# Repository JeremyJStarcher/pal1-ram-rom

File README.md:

#Breaking change #2

# pal1-ram-rom

Configurable RAM ROM for the PAL-1 (kim-1 clone)

This project is still under development to replace the RAM/ROM and IO expansion board with a Pi Pico.

Current state:  The prototype worked after some manual board rework.

Trying to take over the DEN line via software so all ICs except the Pi Pico can be removed from the board.

## KIM-1 Memory Map

* K0 $0000 - $03FF 1024 bytes of RAM (8*6102)
* K1 $0400 - $07FF free
* K2 $0800 - $0BFF free
* K3 $0C00 - $0FFF free
* K4 $1000 - $13FF free
* K5 $1400 - $16FF free
  * $1700 - $173F I/O, timer of 6530-003
  * $1740 - $177F I/O, timer of 6530-002
  * $1780 - $17BF 64 bytes RAM of 6530-003
  * $17C0 - $17FF 64 bytes RAM of 6530-002
* K6 $1800 - $1BFF 1024 bytes ROM of 6530-003
* K7 $1C00 - $1FFF 1024 bytes ROM of 6530-002

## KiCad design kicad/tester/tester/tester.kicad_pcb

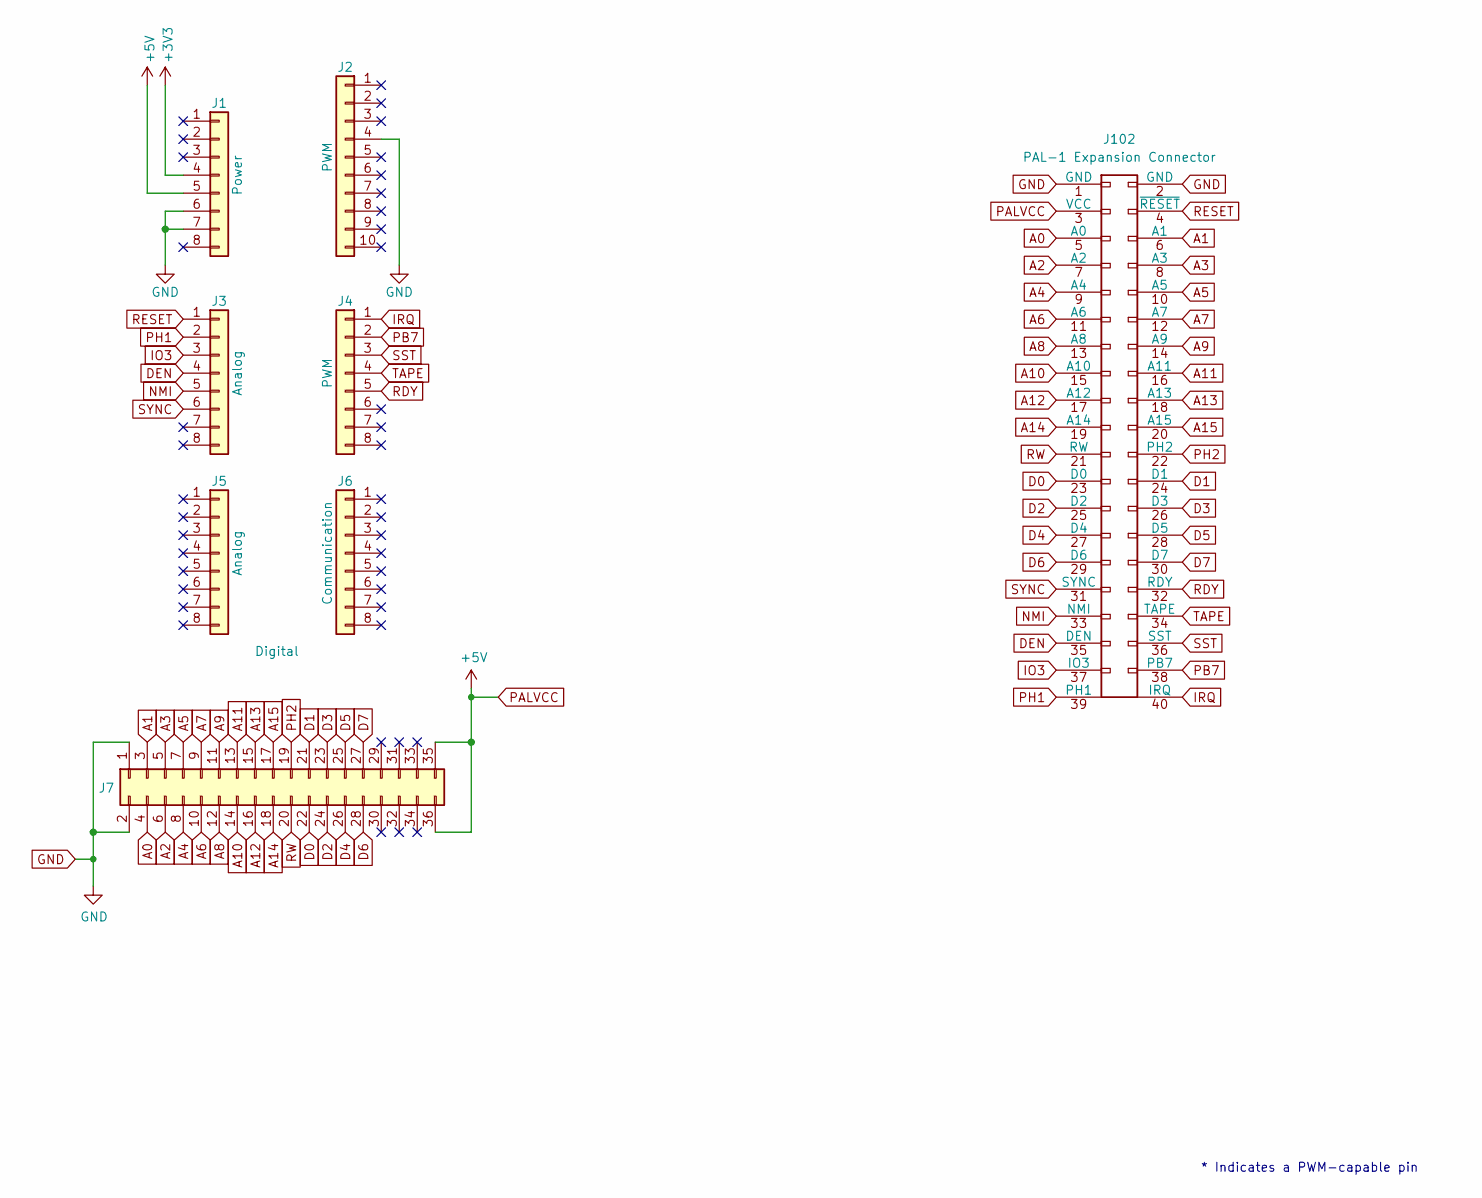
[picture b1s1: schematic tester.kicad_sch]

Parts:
J1: Power; PinSocket_1x08_P2.54mm_Vertical
J2: PWM; PinSocket_1x10_P2.54mm_Vertical
J3, J5: Analog; PinSocket_1x08_P2.54mm_Vertical
J4: PWM; PinSocket_1x08_P2.54mm_Vertical
J6: Communication; PinSocket_1x08_P2.54mm_Vertical
J7: Digital; PinSocket_2x18_P2.54mm_Vertical
J102: PAL-1 Expansion Connector; PinHeader_2x20_P2.54mm_Vertical

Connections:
+3V3: J1.4
A0: J7.4, J102.5 (A0)
A1: J7.3, J102.6 (A1)
A2: J7.6, J102.7 (A2)
A3: J7.5, J102.8 (A3)
A4: J7.8, J102.9 (A4)
A5: J7.7, J102.10 (A5)
A6: J7.10, J102.11 (A6)
A7: J7.9, J102.12 (A7)
A8: J7.12, J102.13 (A8)
A9: J7.11, J102.14 (A9)
A10: J7.14, J102.15 (A10)
A11: J7.13, J102.16 (A11)
A12: J7.16, J102.17 (A12)
A13: J7.15, J102.18 (A13)
A14: J7.18, J102.19 (A14)
A15: J7.17, J102.20 (A15)
D0: J7.22, J102.23 (D0)
D1: J7.21, J102.24 (D1)
D2: J7.24, J102.25 (D2)
D3: J7.23, J102.26 (D3)
D4: J7.26, J102.27 (D4)
D5: J7.25, J102.28 (D5)
D6: J7.28, J102.29 (D6)
D7: J7.27, J102.30 (D7)
DEN: J3.4, J102.35 (DEN)
GND: J1.6, J1.7, J2.4, J7.1, J7.2, J102.1 (GND), J102.2 (GND)
IO3: J3.3, J102.37 (IO3)
IRQ: J4.1, J102.40 (IRQ)
NMI: J3.5, J102.33 (NMI)
PALVCC: J1.5, J7.35, J7.36, J102.3 (VCC)
PB7: J4.2, J102.38 (PB7)
PH1: J3.2, J102.39 (PH1)
PH2: J7.19, J102.22 (PH2)
RDY: J4.5, J102.32 (RDY)
RESET: J3.1, J102.4 (~RESET)
RW: J7.20, J102.21 (RW)
SST: J4.3, J102.36 (SST)
SYNC: J3.6, J102.31 (SYNC)
TAPE: J4.4, J102.34 (TAPE)

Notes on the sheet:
* Indicates a PWM-capable pin

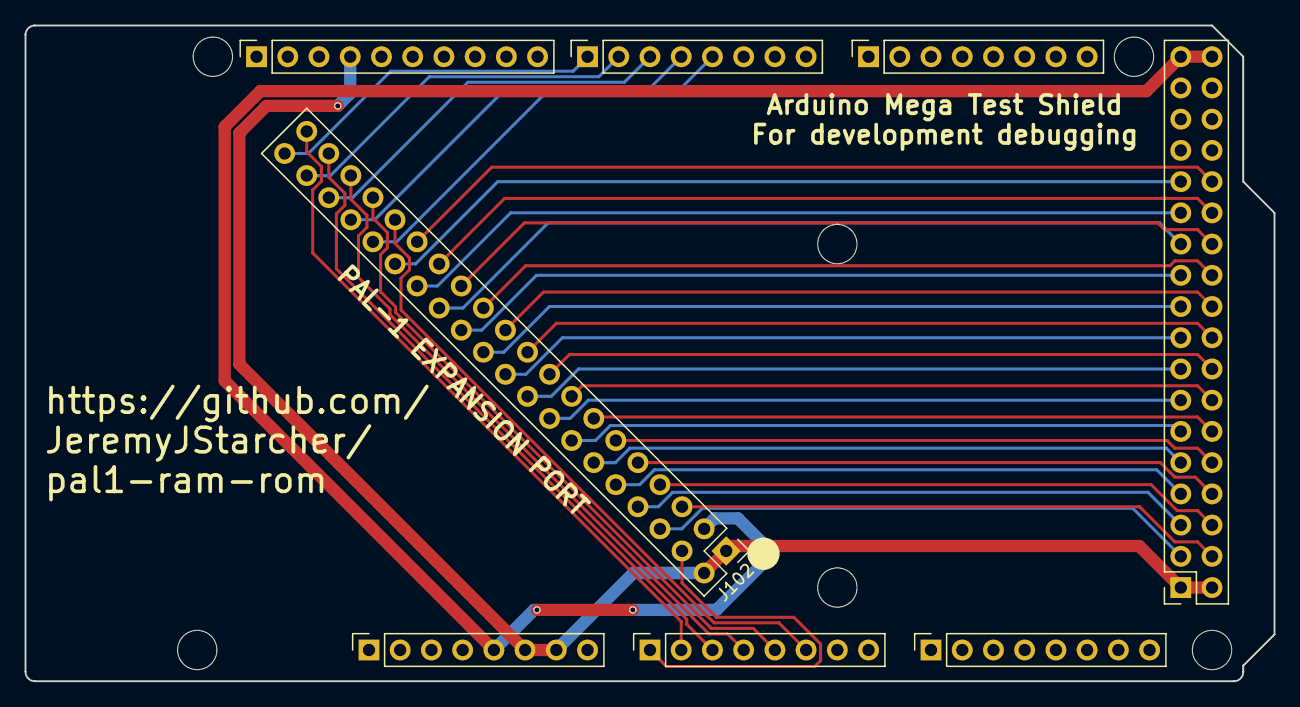
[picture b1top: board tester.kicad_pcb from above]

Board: 2 copper layers, 101.6 x 53.3 mm, 14 parts (0 on the bottom side), 39 nets.

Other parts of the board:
MH1, MH2, MH3, MH4, MH5, MH6: MountingHole_3.2mm

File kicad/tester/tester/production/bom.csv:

Designator,Footprint,Quantity,Value,LCSC Part #
J1,PinSocket_1x08_P2.54mm_Vertical,1,Power,
J102,PinHeader_2x20_P2.54mm_Vertical,1,PAL-1 Expansion Connector,
J2,PinSocket_1x10_P2.54mm_Vertical,1,PWM,
"J3, J5",PinSocket_1x08_P2.54mm_Vertical,2,Analog,
J4,PinSocket_1x08_P2.54mm_Vertical,1,PWM,
J6,PinSocket_1x08_P2.54mm_Vertical,1,Communication,
J7,PinSocket_2x18_P2.54mm_Vertical,1,Digital,

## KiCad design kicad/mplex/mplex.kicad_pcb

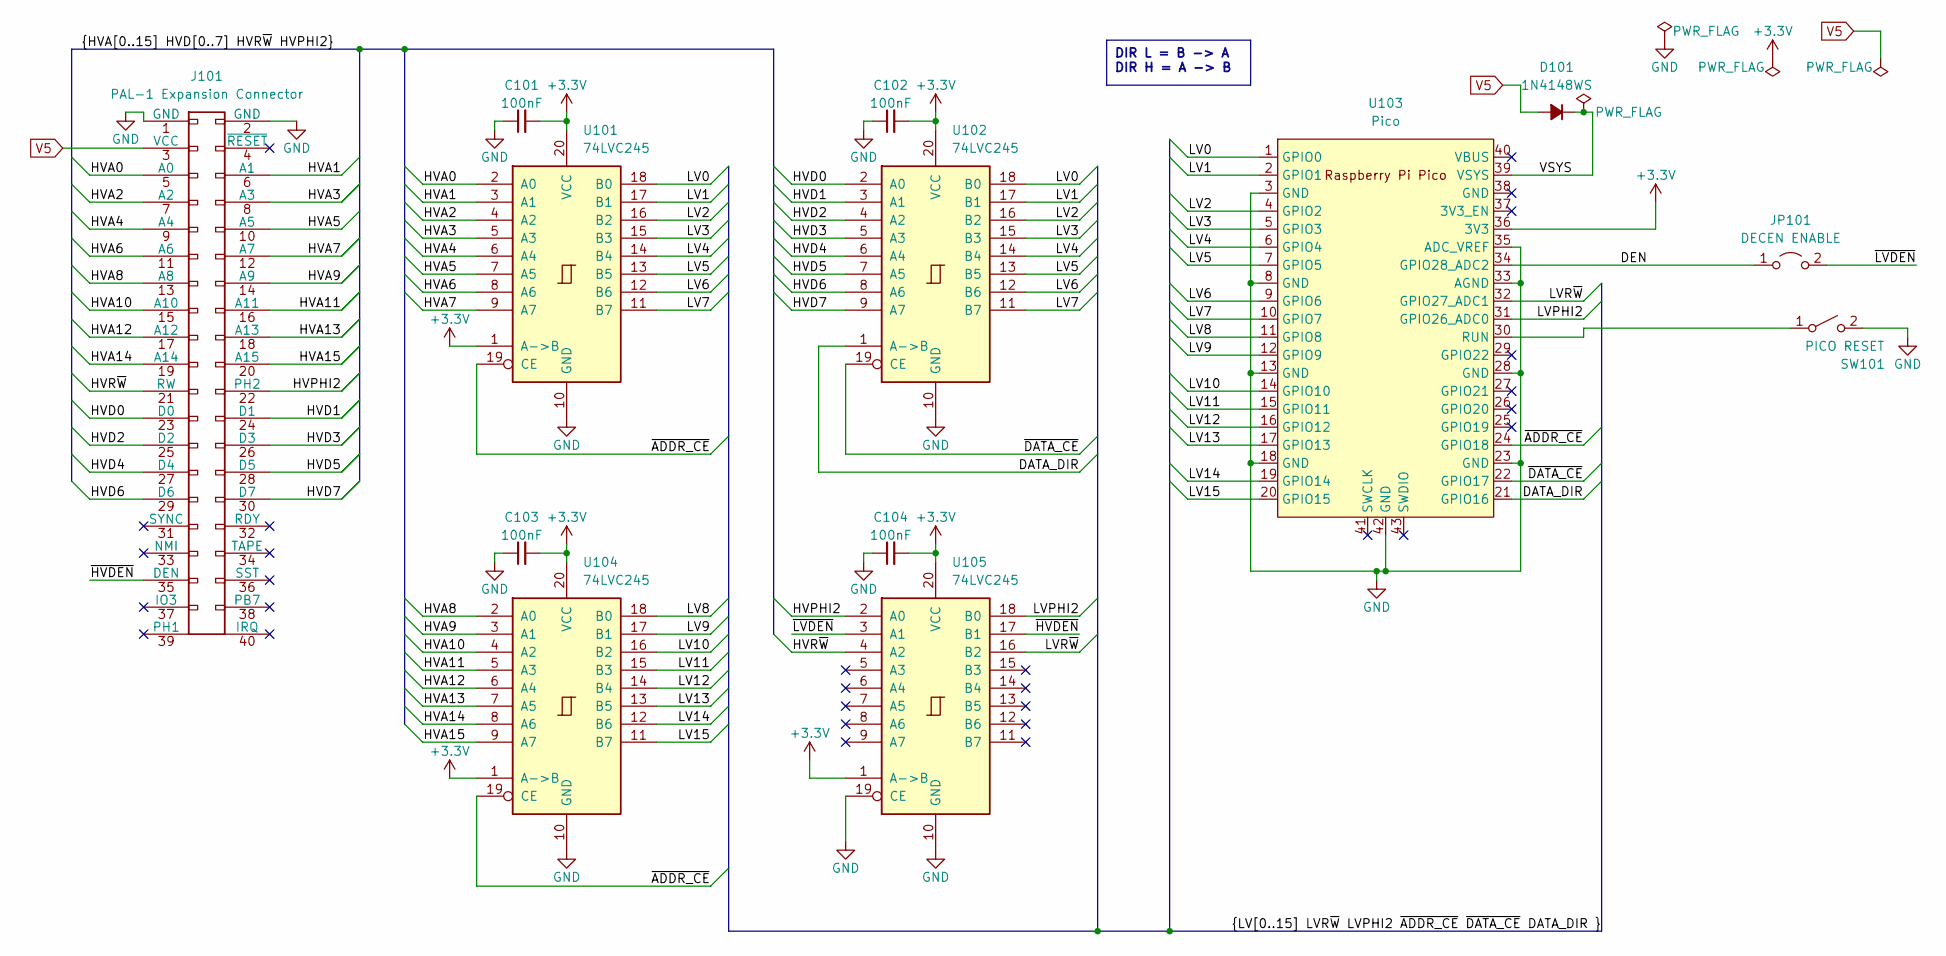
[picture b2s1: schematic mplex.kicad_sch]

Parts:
C101, C102, C103, C104: 100nF; C_Disc_D4.7mm_W2.5mm_P5.00mm
D101: 1N4148WS; D_A-405_P7.62mm_Horizontal; JLCPCB C2128
J101: PAL-1 Expansion Connector; PinHeader_2x20_P2.54mm_Vertical
JP101: DECEN ENABLE; PinHeader_1x02_P2.54mm_Vertical
SW101: PICO RESET; SW_PUSH_6mm_H4.3mm; MFG# TC-6601-6-260G; JLCPCB C2845316
U101, U102, U104, U105: 74LVC245; DIP-20_W7.62mm_Socket_LongPads
U103: Pico; RPi_Pico_SMD_TH

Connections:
+3.3V: C101.2, C102.2, C103.2, C104.2, U101.1 (A->B), U101.20 (VCC), U102.20 (VCC), U103.36 (3V3), U104.1 (A->B), U104.20 (VCC), U105.1 (A->B), U105.20 (VCC)
/DATA_DIR: U102.1 (A->B), U103.21 (GPIO16)
/DEN: JP101.1 (A), U103.34 (GPIO28_ADC2)
/HVA0: J101.5 (A0), U101.2 (A0)
/HVA1: J101.6 (A1), U101.3 (A1)
/HVA2: J101.7 (A2), U101.4 (A2)
/HVA3: J101.8 (A3), U101.5 (A3)
/HVA4: J101.9 (A4), U101.6 (A4)
/HVA5: J101.10 (A5), U101.7 (A5)
/HVA6: J101.11 (A6), U101.8 (A6)
/HVA7: J101.12 (A7), U101.9 (A7)
/HVA8: J101.13 (A8), U104.2 (A0)
/HVA9: J101.14 (A9), U104.3 (A1)
/HVA10: J101.15 (A10), U104.4 (A2)
/HVA11: J101.16 (A11), U104.5 (A3)
/HVA12: J101.17 (A12), U104.6 (A4)
/HVA13: J101.18 (A13), U104.7 (A5)
/HVA14: J101.19 (A14), U104.8 (A6)
/HVA15: J101.20 (A15), U104.9 (A7)
/HVD0: J101.23 (D0), U102.2 (A0)
/HVD1: J101.24 (D1), U102.3 (A1)
/HVD2: J101.25 (D2), U102.4 (A2)
/HVD3: J101.26 (D3), U102.5 (A3)
/HVD4: J101.27 (D4), U102.6 (A4)
/HVD5: J101.28 (D5), U102.7 (A5)
/HVD6: J101.29 (D6), U102.8 (A6)
/HVD7: J101.30 (D7), U102.9 (A7)
/HVPHI2: J101.22 (PH2), U105.2 (A0)
/HVR~W: J101.21 (RW), U105.4 (A2)
/LV0: U101.18 (B0), U102.18 (B0), U103.1 (GPIO0)
/LV1: U101.17 (B1), U102.17 (B1), U103.2 (GPIO1)
/LV2: U101.16 (B2), U102.16 (B2), U103.4 (GPIO2)
/LV3: U101.15 (B3), U102.15 (B3), U103.5 (GPIO3)
/LV4: U101.14 (B4), U102.14 (B4), U103.6 (GPIO4)
/LV5: U101.13 (B5), U102.13 (B5), U103.7 (GPIO5)
/LV6: U101.12 (B6), U102.12 (B6), U103.9 (GPIO6)
/LV7: U101.11 (B7), U102.11 (B7), U103.10 (GPIO7)
/LV8: U103.11 (GPIO8), U104.18 (B0)
/LV9: U103.12 (GPIO9), U104.17 (B1)
/LV10: U103.14 (GPIO10), U104.16 (B2)
/LV11: U103.15 (GPIO11), U104.15 (B3)
/LV12: U103.16 (GPIO12), U104.14 (B4)
/LV13: U103.17 (GPIO13), U104.13 (B5)
/LV14: U103.19 (GPIO14), U104.12 (B6)
/LV15: U103.20 (GPIO15), U104.11 (B7)
/LVPHI2: U103.31 (GPIO26_ADC0), U105.18 (B0)
/LVR~W: U103.32 (GPIO27_ADC1), U105.16 (B2)
/VSYS: D101.1 (K), U103.39 (VSYS)
/~ADDR_CE: U101.19 (CE), U103.24 (GPIO18), U104.19 (CE)
/~DATA_CE: U102.19 (CE), U103.22 (GPIO17)
/~HVDEN: J101.35 (DEN), U105.17 (B1)
/~LVDEN: JP101.2 (B), U105.3 (A1)
unnamed: SW101.1 (A), U103.30 (RUN)
V5: D101.2 (A), J101.3 (VCC)

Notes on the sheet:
DIR L = B -> A DIR H = A -> B

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
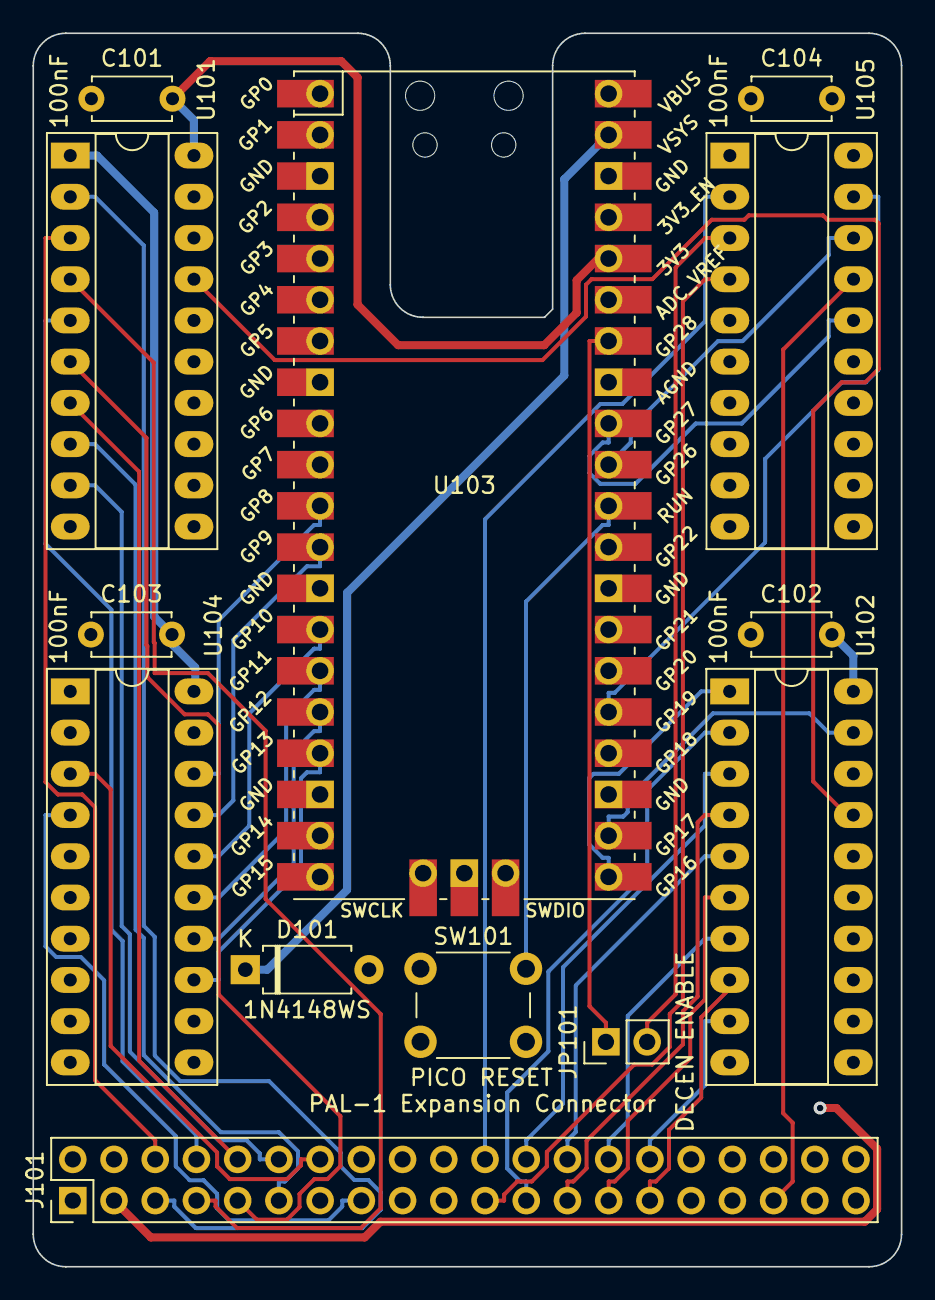
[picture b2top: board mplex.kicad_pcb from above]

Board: 4 copper layers, 53.5 x 76.0 mm, 13 parts (0 on the bottom side), 56 nets.

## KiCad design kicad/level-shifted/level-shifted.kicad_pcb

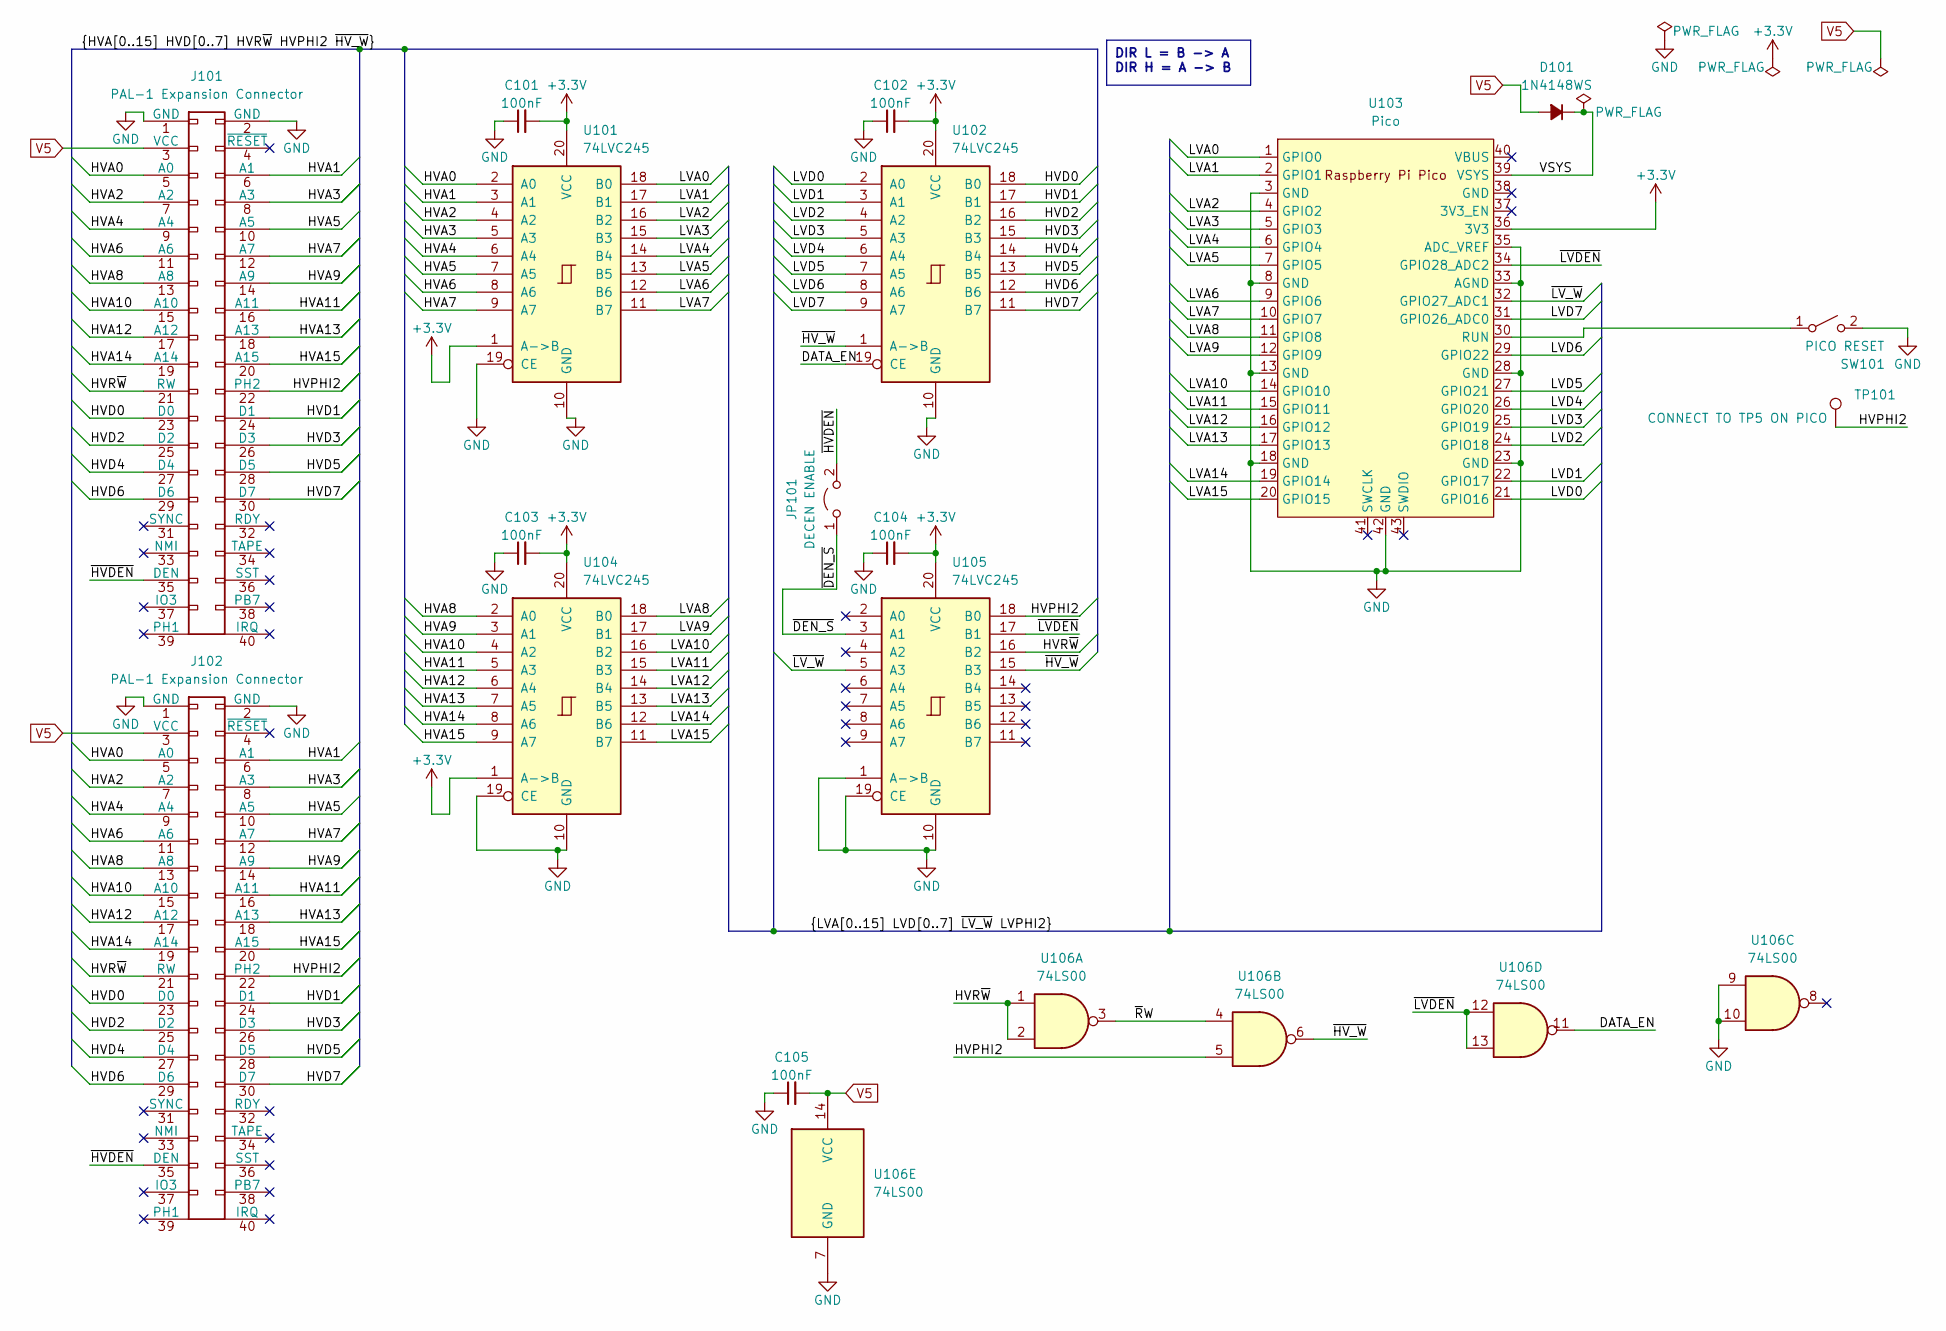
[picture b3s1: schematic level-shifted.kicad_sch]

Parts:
C101, C102, C103, C104: 100nF; C_Disc_D4.7mm_W2.5mm_P5.00mm
C105: 100nF; C_1812_4532Metric_Pad1.57x3.40mm_HandSolder
D101: 1N4148WS; D_A-405_P7.62mm_Horizontal; JLCPCB C2128
J101, J102: PAL-1 Expansion Connector; PinHeader_2x20_P2.54mm_Vertical
JP101: DECEN ENABLE; PinHeader_1x02_P2.54mm_Vertical
SW101: PICO RESET; SW_PUSH_6mm_H4.3mm; MFG# TC-6601-6-260G; JLCPCB C2845316
TP101: CONNECT TO TP5 ON PICO; TestPoint_Pad_2.5x2.5mm
U101, U102, U104, U105: 74LVC245; DIP-20_W7.62mm_Socket_LongPads
U103: Pico; RPi_Pico_SMD_TH
U106: 74LS00; DIP-14_W8.89mm_SMDSocket_LongPads

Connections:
+3.3V: C101.2, C102.2, C103.2, C104.2, U101.1 (A->B), U101.20 (VCC), U102.20 (VCC), U103.36 (3V3), U104.1 (A->B), U104.20 (VCC), U105.20 (VCC)
/DATA_EN: U102.19 (CE), U106.11
/HVA0: J101.5 (A0), J102.5 (A0), U101.2 (A0)
/HVA1: J101.6 (A1), J102.6 (A1), U101.3 (A1)
/HVA2: J101.7 (A2), J102.7 (A2), U101.4 (A2)
/HVA3: J101.8 (A3), J102.8 (A3), U101.5 (A3)
/HVA4: J101.9 (A4), J102.9 (A4), U101.6 (A4)
/HVA5: J101.10 (A5), J102.10 (A5), U101.7 (A5)
/HVA6: J101.11 (A6), J102.11 (A6), U101.8 (A6)
/HVA7: J101.12 (A7), J102.12 (A7), U101.9 (A7)
/HVA8: J101.13 (A8), J102.13 (A8), U104.2 (A0)
/HVA9: J101.14 (A9), J102.14 (A9), U104.3 (A1)
/HVA10: J101.15 (A10), J102.15 (A10), U104.4 (A2)
/HVA11: J101.16 (A11), J102.16 (A11), U104.5 (A3)
/HVA12: J101.17 (A12), J102.17 (A12), U104.6 (A4)
/HVA13: J101.18 (A13), J102.18 (A13), U104.7 (A5)
/HVA14: J101.19 (A14), J102.19 (A14), U104.8 (A6)
/HVA15: J101.20 (A15), J102.20 (A15), U104.9 (A7)
/HVD0: J101.23 (D0), J102.23 (D0), U102.18 (B0)
/HVD1: J101.24 (D1), J102.24 (D1), U102.17 (B1)
/HVD2: J101.25 (D2), J102.25 (D2), U102.16 (B2)
/HVD3: J101.26 (D3), J102.26 (D3), U102.15 (B3)
/HVD4: J101.27 (D4), J102.27 (D4), U102.14 (B4)
/HVD5: J101.28 (D5), J102.28 (D5), U102.13 (B5)
/HVD6: J101.29 (D6), J102.29 (D6), U102.12 (B6)
/HVD7: J101.30 (D7), J102.30 (D7), U102.11 (B7)
/HVPHI2: J101.22 (PH2), J102.22 (PH2), TP101.1, U105.18 (B0), U106.5
/HVR~W: J101.21 (RW), J102.21 (RW), U105.16 (B2), U106.1, U106.2
/LVA0: U101.18 (B0), U103.1 (GPIO0)
/LVA1: U101.17 (B1), U103.2 (GPIO1)
/LVA2: U101.16 (B2), U103.4 (GPIO2)
/LVA3: U101.15 (B3), U103.5 (GPIO3)
/LVA4: U101.14 (B4), U103.6 (GPIO4)
/LVA5: U101.13 (B5), U103.7 (GPIO5)
/LVA6: U101.12 (B6), U103.9 (GPIO6)
/LVA7: U101.11 (B7), U103.10 (GPIO7)
/LVA8: U103.11 (GPIO8), U104.18 (B0)
/LVA9: U103.12 (GPIO9), U104.17 (B1)
/LVA10: U103.14 (GPIO10), U104.16 (B2)
/LVA11: U103.15 (GPIO11), U104.15 (B3)
/LVA12: U103.16 (GPIO12), U104.14 (B4)
/LVA13: U103.17 (GPIO13), U104.13 (B5)
/LVA14: U103.19 (GPIO14), U104.12 (B6)
/LVA15: U103.20 (GPIO15), U104.11 (B7)
/LVD0: U102.2 (A0), U103.21 (GPIO16)
/LVD1: U102.3 (A1), U103.22 (GPIO17)
/LVD2: U102.4 (A2), U103.24 (GPIO18)
/LVD3: U102.5 (A3), U103.25 (GPIO19)
/LVD4: U102.6 (A4), U103.26 (GPIO20)
/LVD5: U102.7 (A5), U103.27 (GPIO21)
/LVD6: U102.8 (A6), U103.29 (GPIO22)
/LVD7: U102.9 (A7), U103.31 (GPIO26_ADC0)
/VSYS: D101.1 (K), U103.39 (VSYS)
/~DEN_S: JP101.1 (A), U105.3 (A1)
/~HVDEN: J101.35 (DEN), J102.35 (DEN), JP101.2 (B)
/~HV_W: U102.1 (A->B), U105.15 (B3), U106.6
/~LVDEN: U103.34 (GPIO28_ADC2), U105.17 (B1), U106.12, U106.13
/~LV_W: U103.32 (GPIO27_ADC1), U105.5 (A3)
/~RW: U106.3, U106.4
GND: C101.1, C102.1, C103.1, C104.1, C105.1, J101.1 (GND), J101.2 (GND), J102.1 (GND), J102.2 (GND), SW101.2 (B), U101.10 (GND), U101.19 (CE), U102.10 (GND), U103.3 (GND), U103.8 (GND), U103.13 (GND), U103.18 (GND), U103.23 (GND), U103.28 (GND), U103.33 (AGND), U103.35 (ADC_VREF), U103.42 (GND), U104.10 (GND), U104.19 (CE), U105.1 (A->B), U105.10 (GND), U105.19 (CE), U106.7 (GND), U106.9, U106.10
unnamed: SW101.1 (A), U103.30 (RUN)
V5: C105.2, D101.2 (A), J101.3 (VCC), J102.3 (VCC), U106.14 (VCC)

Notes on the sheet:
DIR L = B -> A DIR H = A -> B

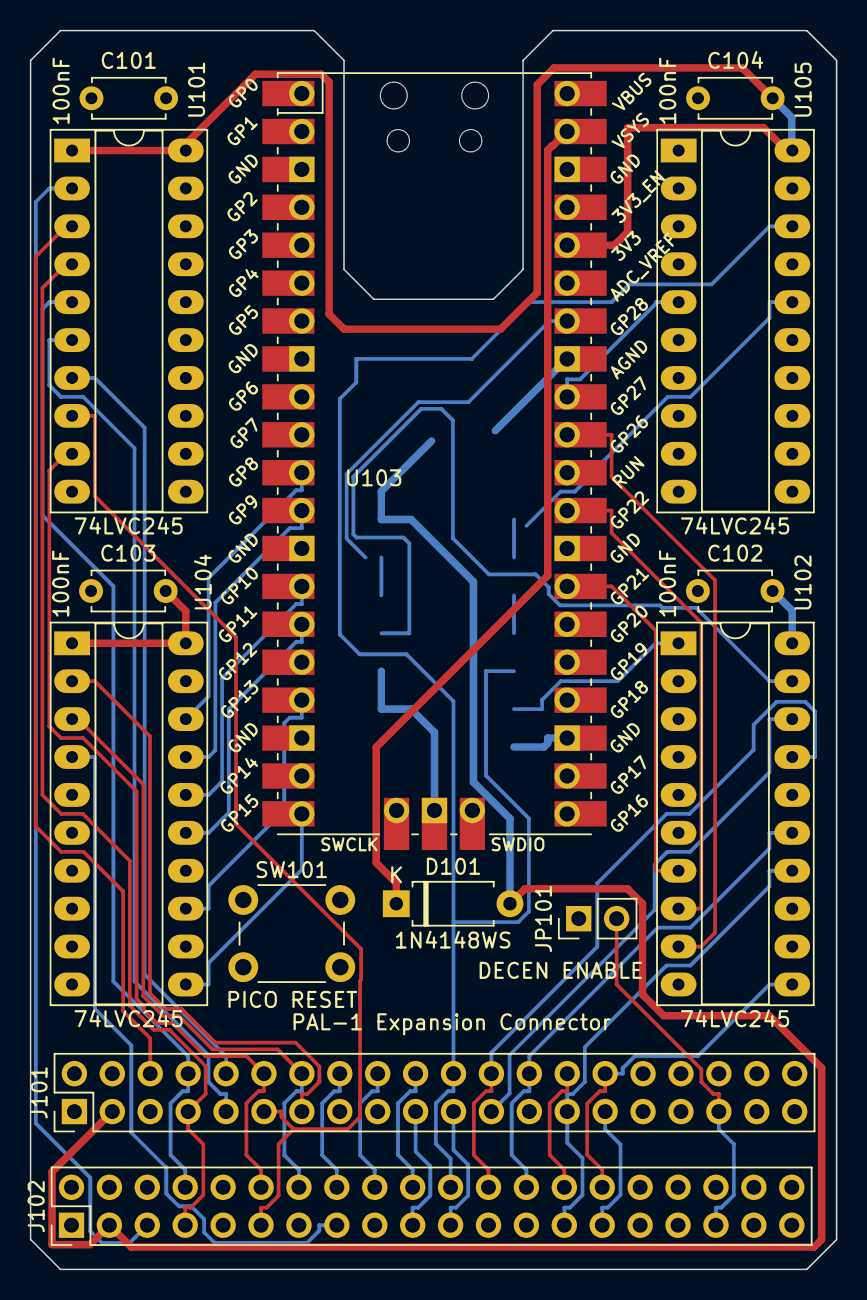
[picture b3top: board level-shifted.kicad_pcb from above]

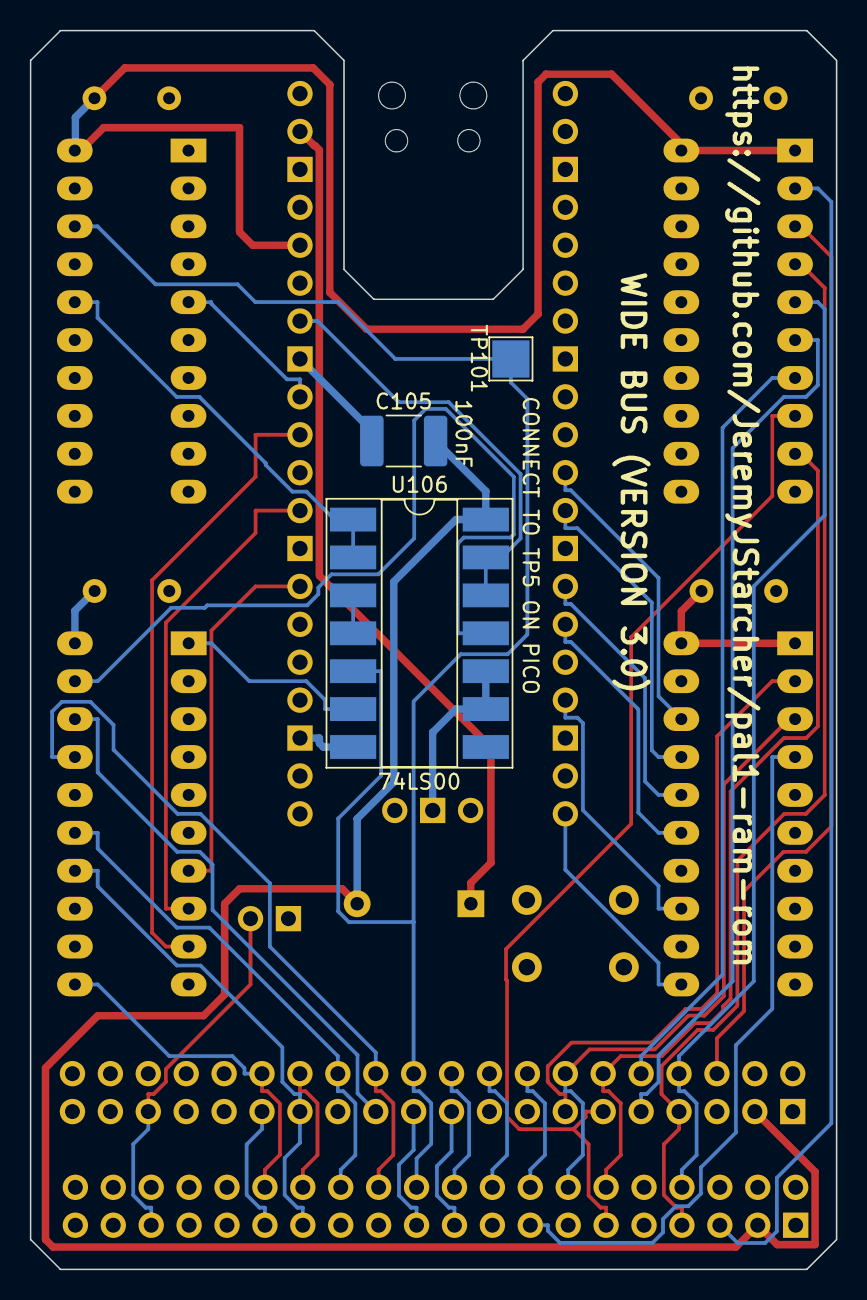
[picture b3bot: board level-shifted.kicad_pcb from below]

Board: 4 copper layers, 54.0 x 83.0 mm, 17 parts (3 on the bottom side), 62 nets.

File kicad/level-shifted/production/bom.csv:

Designator,Footprint,Quantity,Value,LCSC Part #
"C101, C102, C103, C104",C_Disc_D4.7mm_W2.5mm_P5.00mm,4,100nF,
C105,1812,1,100nF,
D101,D_A-405_P7.62mm_Horizontal,1,1N4148WS,
"J101, J102",PinHeader_2x20_P2.54mm_Vertical,2,PAL-1 Expansion Connector,
JP101,PinHeader_1x02_P2.54mm_Vertical,1,DECEN ENABLE,
SW101,SW_PUSH_6mm_H4.3mm,1,PICO RESET,
TP101,TestPoint_Pad_2.5x2.5mm,1,CONNECT TO TP5 ON PICO,
"U101, U102, U104, U105",DIP-20_W7.62mm_Socket_LongPads,4,74LVC245,
U103,RPi_Pico_SMD_TH,1,Pico,
U106,DIP-14_W8.89mm_SMDSocket_LongPads,1,74LS00,

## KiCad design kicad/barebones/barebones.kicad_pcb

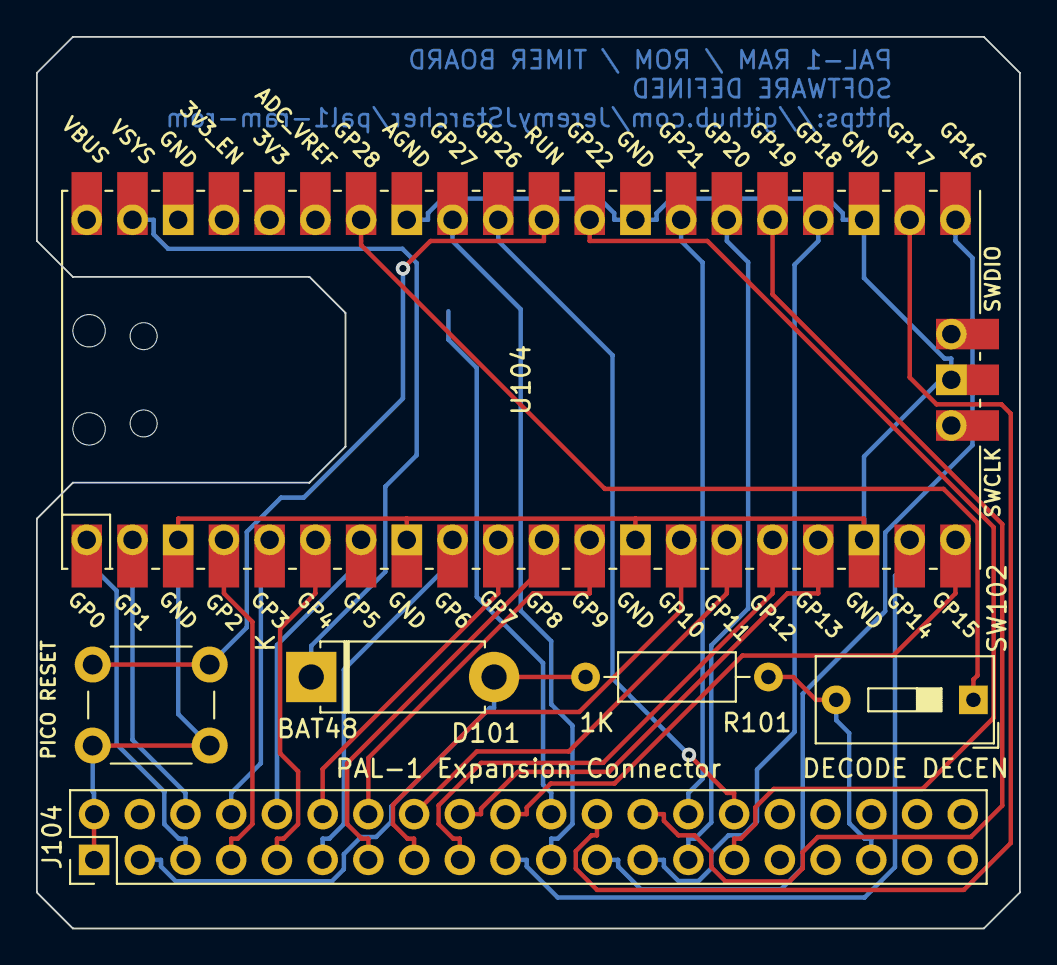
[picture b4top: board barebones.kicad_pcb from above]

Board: 2 copper layers, 54.6 x 49.5 mm, 7 parts (1 on the bottom side), 32 nets.

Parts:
D101: BAT48; D_5W_P10.16mm_Horizontal
J104: PAL-1 Expansion Connector; PinHeader_2x20_P2.54mm_Vertical
R101: 1K; R_Axial_DIN0207_L6.3mm_D2.5mm_P10.16mm_Horizontal
SW101: PICO RESET; SW_PUSH_6mm
SW102: SW_DIP_x01; SW_DIP_SPSTx01_Slide_9.78x4.72mm_W7.62mm_P2.54mm
TP101: CONNECT TO TP5 ON PICO; TestPoint_Pad_2.5x2.5mm
U104: Pico; RPi_Pico_SMD_TH

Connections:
A0: J104.5 (A0), U104.1 (GPIO0)
A1: J104.6 (A1), U104.2 (GPIO1)
A2: J104.7 (A2), U104.4 (GPIO2)
A3: J104.8 (A3), U104.5 (GPIO3)
A4: J104.9 (A4), U104.6 (GPIO4)
A5: J104.10 (A5), U104.7 (GPIO5)
A6: J104.11 (A6), U104.9 (GPIO6)
A7: J104.12 (A7), U104.10 (GPIO7)
A8: J104.13 (A8), U104.11 (GPIO8)
A9: J104.14 (A9), U104.12 (GPIO9)
A10: J104.15 (A10), U104.14 (GPIO10)
A11: J104.16 (A11), U104.15 (GPIO11)
A12: J104.17 (A12), U104.16 (GPIO12)
A13: J104.18 (A13), U104.17 (GPIO13)
A14: J104.19 (A14), U104.19 (GPIO14)
A15: J104.20 (A15), U104.20 (GPIO15)
D0: J104.23 (D0), U104.21 (GPIO16)
D1: J104.24 (D1), U104.22 (GPIO17)
D2: J104.25 (D2), U104.24 (GPIO18)
D3: J104.26 (D3), U104.25 (GPIO19)
D4: J104.27 (D4), U104.26 (GPIO20)
D5: J104.28 (D5), U104.27 (GPIO21)
D6: J104.29 (D6), U104.29 (GPIO22)
D7: J104.30 (D7), U104.31 (GPIO26_ADC0)
DEN: J104.35 (DEN), R101.2, SW102.2
GND: J104.1 (GND), J104.2 (GND), SW101.2 (B), U104.3 (GND), U104.8 (GND), U104.13 (GND), U104.18 (GND), U104.23 (GND), U104.28 (GND), U104.33 (AGND), U104.42 (GND)
unnamed: D101.1 (K), U104.39 (VSYS)
unnamed: SW101.1 (A), U104.30 (RUN)
unnamed: SW102.1, U104.34 (GPIO28_ADC2)
PHI2: J104.22 (PH2), TP101.1
RW: J104.21 (RW), U104.32 (GPIO27_ADC1)
V5: D101.2 (A), J104.3 (VCC), R101.1

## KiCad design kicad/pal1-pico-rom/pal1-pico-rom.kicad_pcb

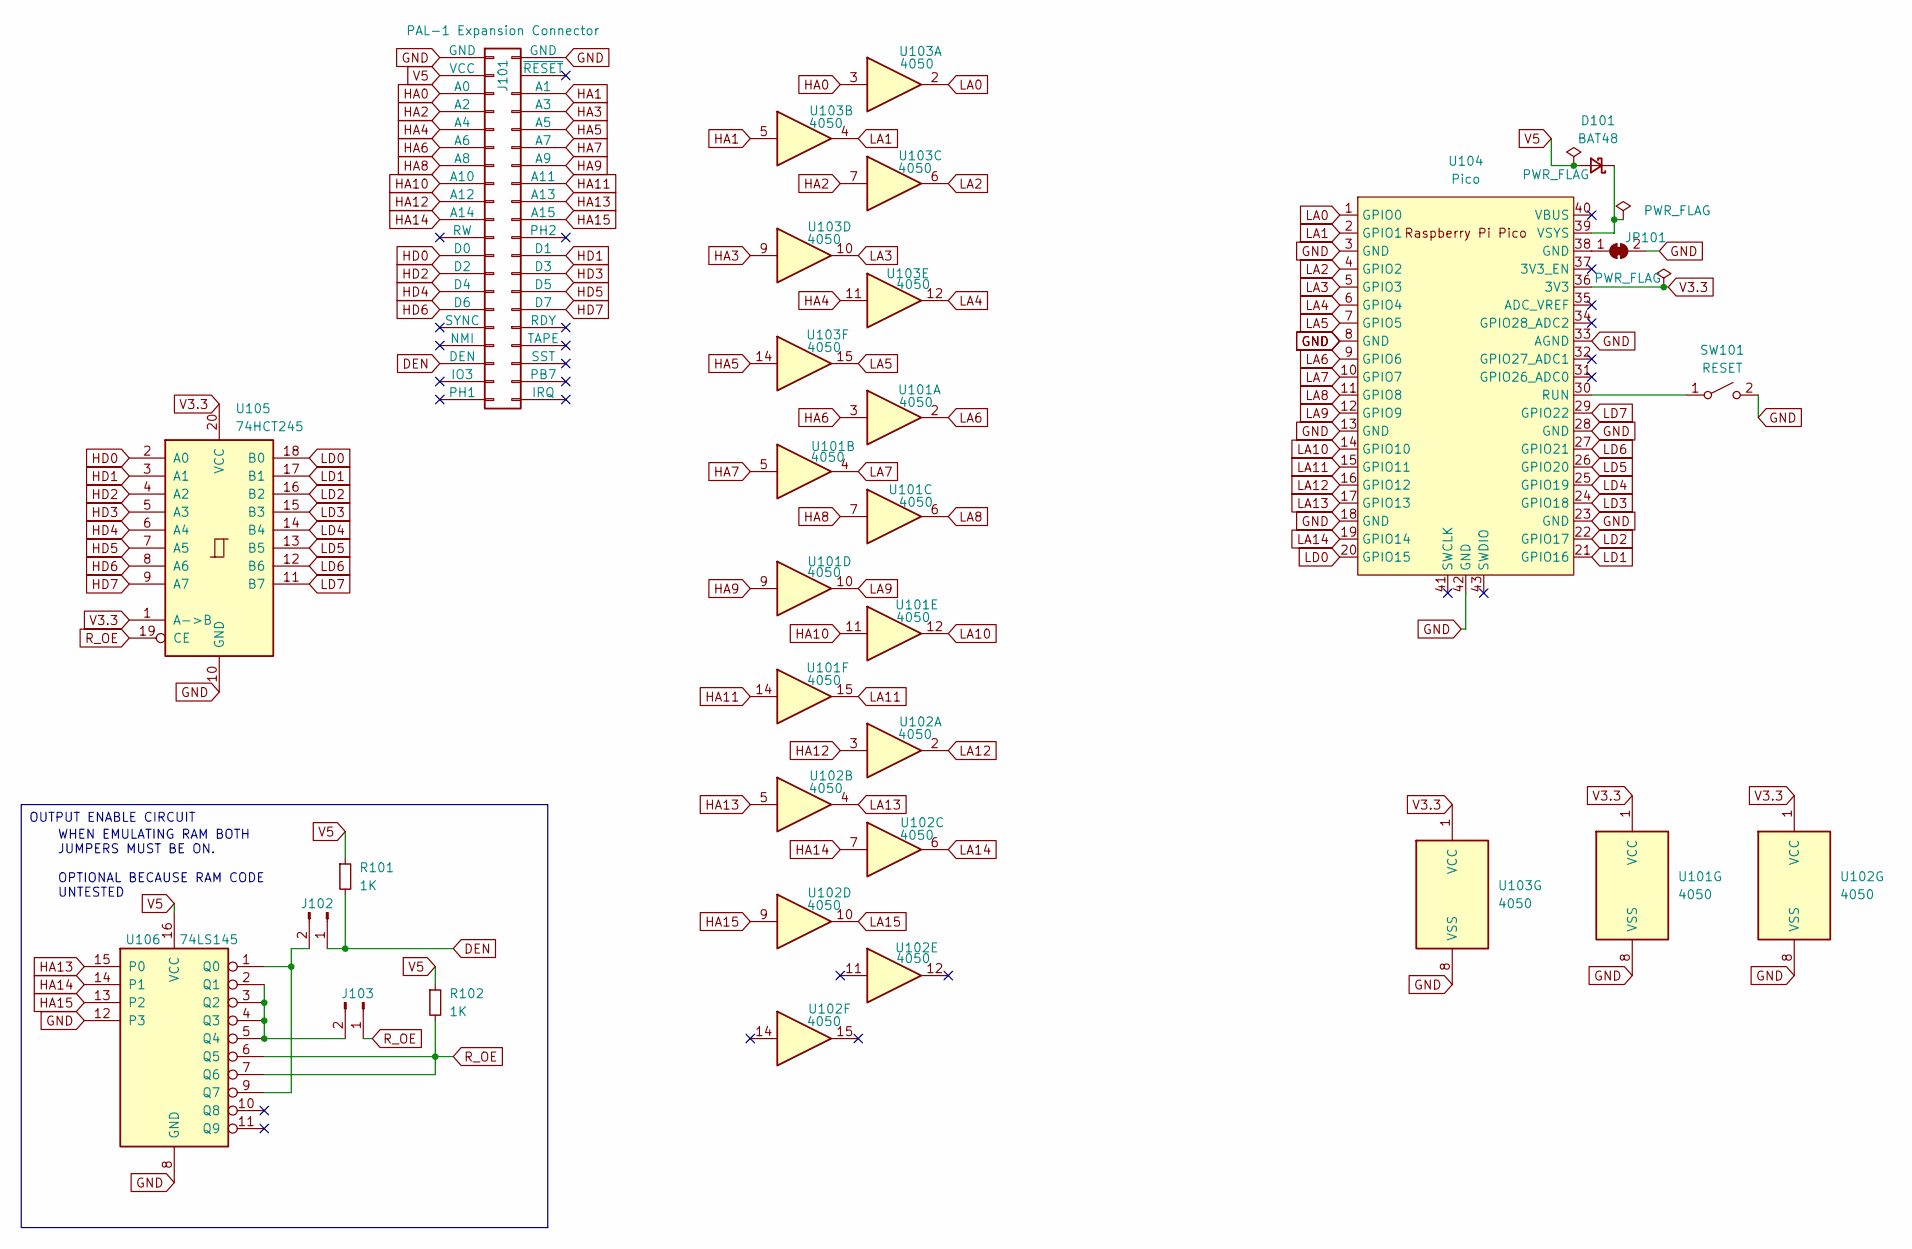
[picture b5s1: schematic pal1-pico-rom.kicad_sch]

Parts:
D101: BAT48; D_5W_P10.16mm_Horizontal
J101: PAL-1 Expansion Connector; PinHeader_2x20_P2.54mm_Horizontal
J102, J103: Conn_01x02_Pin; PinHeader_1x02_P2.54mm_Vertical
JP101: SolderJumper_2_Bridged; SolderJumper-2_P1.3mm_Bridged2Bar_RoundedPad1.0x1.5mm
R101, R102: 1K; R_Axial_DIN0204_L3.6mm_D1.6mm_P5.08mm_Horizontal
SW101: RESET; SW_PUSH_6mm
U101, U102, U103: 4050; DIP-16_W7.62mm_Socket_LongPads
U104: Pico; RPi_Pico_SMD_TH
U105: 74HCT245; DIP-20_W7.62mm_Socket_LongPads; Digispark 296-8503-5-ND
U106: 74LS145; DIP-16_W7.62mm_Socket_LongPads

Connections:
DEN: J101.35 (DEN), J102.1, R101.2
GND: J101.1 (GND), J101.2 (GND), JP101.2 (B), SW101.2 (B), U101.8 (VSS), U102.8 (VSS), U103.8 (VSS), U104.3 (GND), U104.8 (GND), U104.13 (GND), U104.18 (GND), U104.23 (GND), U104.28 (GND), U104.33 (AGND), U104.42 (GND), U105.10 (GND), U106.8 (GND), U106.12 (P3)
HA0: J101.5 (A0), U103.3
HA1: J101.6 (A1), U103.5
HA2: J101.7 (A2), U103.7
HA3: J101.8 (A3), U103.9
HA4: J101.9 (A4), U103.11
HA5: J101.10 (A5), U103.14
HA6: J101.11 (A6), U101.3
HA7: J101.12 (A7), U101.5
HA8: J101.13 (A8), U101.7
HA9: J101.14 (A9), U101.9
HA10: J101.15 (A10), U101.11
HA11: J101.16 (A11), U101.14
HA12: J101.17 (A12), U102.3
HA13: J101.18 (A13), U102.5, U106.15 (P0)
HA14: J101.19 (A14), U102.7, U106.14 (P1)
HA15: J101.20 (A15), U102.9, U106.13 (P2)
HD0: J101.23 (D0), U105.2 (A0)
HD1: J101.24 (D1), U105.3 (A1)
HD2: J101.25 (D2), U105.4 (A2)
HD3: J101.26 (D3), U105.5 (A3)
HD4: J101.27 (D4), U105.6 (A4)
HD5: J101.28 (D5), U105.7 (A5)
HD6: J101.29 (D6), U105.8 (A6)
HD7: J101.30 (D7), U105.9 (A7)
LA0: U103.2, U104.1 (GPIO0)
LA1: U103.4, U104.2 (GPIO1)
LA2: U103.6, U104.4 (GPIO2)
LA3: U103.10, U104.5 (GPIO3)
LA4: U103.12, U104.6 (GPIO4)
LA5: U103.15, U104.7 (GPIO5)
LA6: U101.2, U104.9 (GPIO6)
LA7: U101.4, U104.10 (GPIO7)
LA8: U101.6, U104.11 (GPIO8)
LA9: U101.10, U104.12 (GPIO9)
LA10: U101.12, U104.14 (GPIO10)
LA11: U101.15, U104.15 (GPIO11)
LA12: U102.2, U104.16 (GPIO12)
LA13: U102.4, U104.17 (GPIO13)
LA14: U102.6, U104.19 (GPIO14)
LA15: U102.10
LD0: U104.20 (GPIO15), U105.18 (B0)
LD1: U104.21 (GPIO16), U105.17 (B1)
LD2: U104.22 (GPIO17), U105.16 (B2)
LD3: U104.24 (GPIO18), U105.15 (B3)
LD4: U104.25 (GPIO19), U105.14 (B4)
LD5: U104.26 (GPIO20), U105.13 (B5)
LD6: U104.27 (GPIO21), U105.12 (B6)
LD7: U104.29 (GPIO22), U105.11 (B7)
unnamed: D101.1 (K), U104.39 (VSYS)
unnamed: J102.2, U106.1 (Q0), U106.9 (Q7)
unnamed: J103.2, U106.2 (Q1), U106.3 (Q2), U106.4 (Q3), U106.5 (Q4)
unnamed: JP101.1 (A), U104.38 (GND)
unnamed: SW101.1 (A), U104.30 (RUN)
R_OE: J103.1, R102.2, U105.19 (CE), U106.6 (Q5), U106.7 (Q6)
V3.3: U101.1 (VCC), U102.1 (VCC), U103.1 (VCC), U104.36 (3V3), U105.1 (A->B), U105.20 (VCC)
V5: D101.2 (A), J101.3 (VCC), R101.1, R102.1, U106.16 (VCC)

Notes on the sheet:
OUTPUT ENABLE CIRCUIT
WHEN EMULATING RAM BOTH JUMPERS MUST BE ON. OPTIONAL BECAUSE RAM CODE UNTESTED
